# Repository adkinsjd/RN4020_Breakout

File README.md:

This is a breakout board for the Microchip (Roving Networks) RN4020 BLE
module.

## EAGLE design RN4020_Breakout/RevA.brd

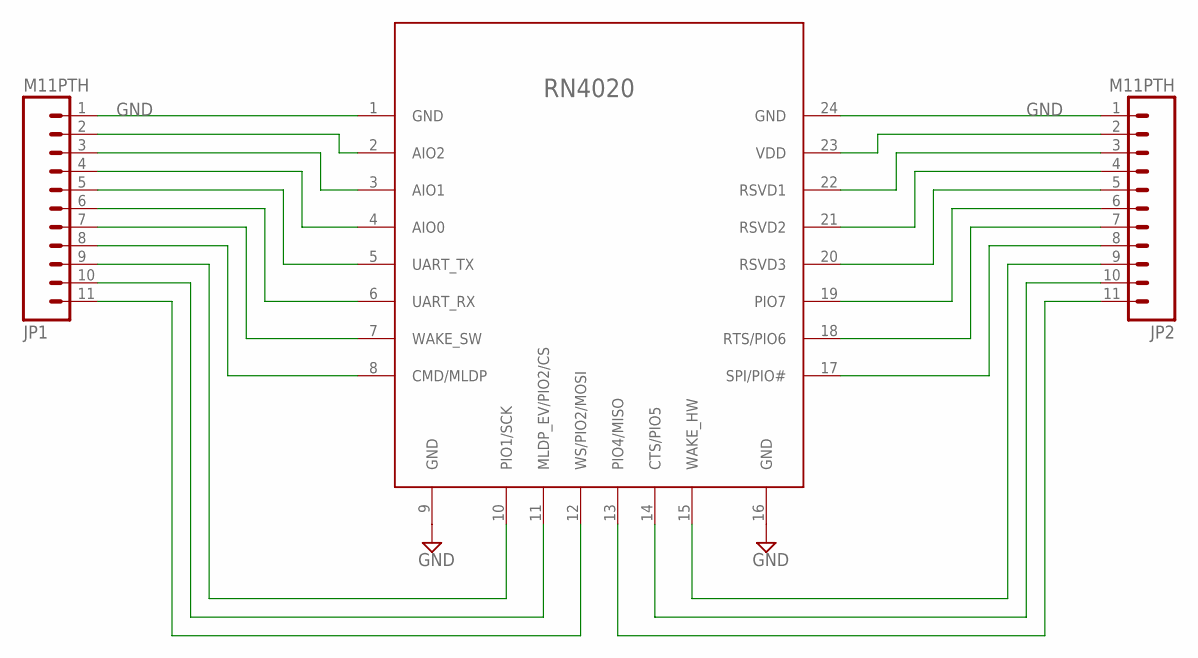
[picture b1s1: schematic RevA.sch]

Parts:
JP1, JP2: M11PTH; 1X11
U$1: RN4020

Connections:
GND: JP1.1, JP2.1, U$1.1 (GND), U$1.9 (GND), U$1.16 (GND), U$1.24 (GND)
unnamed: JP1.2, U$1.2 (AIO2)
unnamed: JP1.3, U$1.3 (AIO1)
unnamed: JP1.4, U$1.4 (AIO0)
unnamed: JP1.5, U$1.5 (UART_TX)
unnamed: JP1.6, U$1.6 (UART_RX)
unnamed: JP1.7, U$1.7 (WAKE_SW)
unnamed: JP1.8, U$1.8 (CMD/MLDP)
unnamed: JP1.9, U$1.10 (PIO1/SCK)
unnamed: JP1.10, U$1.11 (MLDP_EV/PIO2/CS)
unnamed: JP1.11, U$1.12 (WS/PIO2/MOSI)
unnamed: JP2.3, U$1.22 (RSVD1)
unnamed: JP2.4, U$1.21 (RSVD2)
unnamed: JP2.5, U$1.20 (RSVD3)
unnamed: JP2.6, U$1.19 (PIO7)
unnamed: JP2.7, U$1.18 (RTS/PIO6)
unnamed: JP2.8, U$1.17 (SPI/PIO#)
unnamed: JP2.9, U$1.15 (WAKE_HW)
unnamed: JP2.10, U$1.14 (CTS/PIO5)
unnamed: JP2.11, U$1.13 (PIO4/MISO)
VDD: JP2.2, U$1.23 (VDD)

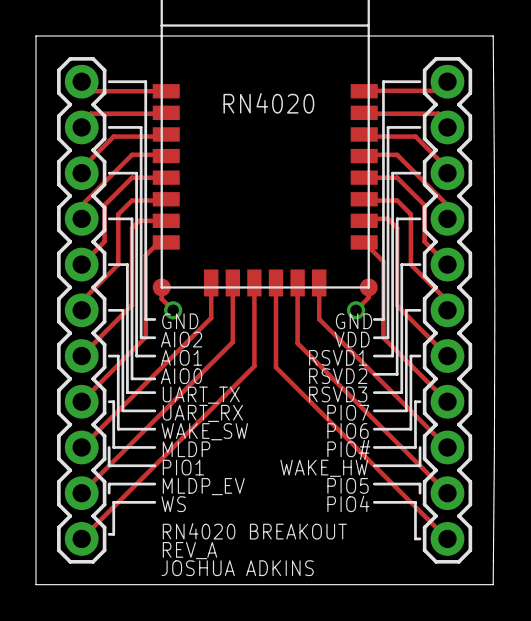
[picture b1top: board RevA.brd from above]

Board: 2 copper layers, 25.5 x 30.5 mm, 3 parts (0 on the bottom side), 21 nets.

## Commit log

2014-08-04 First commit - README
2014-08-11 Created first version of the breakout board
2014-08-11 Added board artwork
2014-08-12 Made artwork revisions to fit Itead manufacturing limitations
2014-08-12 Added gerber files and zipped folder sent to board house

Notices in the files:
parts and their libraries:
SparkFun-Connectors: Licensing: CC v3.0 Share-Alike You are welcome to use this library for commercial purposes.
